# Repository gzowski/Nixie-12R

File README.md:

# Nixie-12R - Keyboard/GamePad

* Available to purchase from: https://www.etsy.com/uk/shop/PhoenixCustomBoards

* 11 key ortholinear keyboard
* 1 Rotary encoder in the top right
* OLED Display for displaying layer selected
* Pro Micro compatible
  
### [Info](#Info) || [Parts](#Parts) || [Assembly Guide](#Assembly-Guide)

## Info

* PCB Files within PCB folder, created with KiCad.
* VIA config export and via.json design files in VIA folder
* QMK firmware within QMK/QMK_Firmware/Keyboards/Nixie12r, can be pasted into a local copy of qmk repo and made.
* 3D printable case within Case folder

## Parts

| Part | Quantity     | Description                | 
| :-------- | :------- | :------------------------- |
| Diodes| 12  | Through-hole 1N4148 |
| Microcontroller | 1 | Pro-Micro compatible |
| MX Switches | 11 | Cherry MX compatible switches |
| EC11 | 1 | Rotary Encoder |
| MJTP1117 | 1 | Angled reset switch |
| Keycaps | 1 | 11x1u switches |
| OLED Display | 1 | 128x32 OLED (SSD1306) |

## Assembly Guide

* Insert all switches into the top plate and put to the side
* Diode installation: insert from top of the pcb so diodes are visible from the top
* Reset switch: insert switch on top and solder from underside, remove legs beforehand for clearance.
* Microcontroller needs to be positioned with the top facing the PCB, upsidedown (Test controller beforehand and flash firmware using QMK)
* Place OLED Display on top of PCB and solder from underside.
* Place the rotary encoder on the top side and solder all points ensuring it stays flush to the board.
* Press down the top plate with switches and stabalisers down on the middle plate ensuring that all the switches sit flush against the middle plate.
* Turn board over and proceed to solder switches to the board
* Connect USB to keyboard and check all keys are functional, this is assuming you've already flashed the firmware to the MCU.

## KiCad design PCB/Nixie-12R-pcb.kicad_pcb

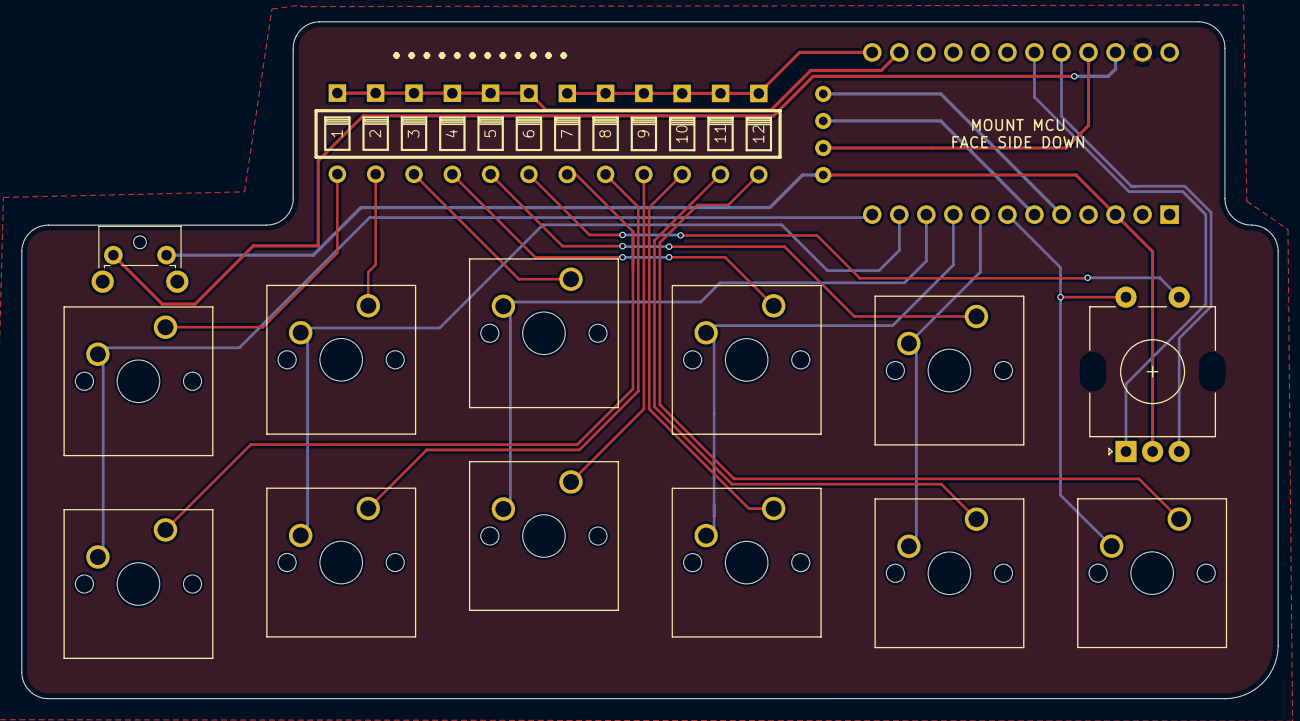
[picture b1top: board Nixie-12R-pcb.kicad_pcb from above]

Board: 2 copper layers, 118.1 x 63.6 mm, 27 parts (1 on the bottom side), 27 nets.

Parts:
1, 2: Diode
3, 4, 5, 6, 7, 8, 9, 10, 11, 12: VAL**; Diode
K1, K2, K3, K4, K5, K7, K8, K9, K10, K11, K12: Blank; SW_Cherry_MX_2.00u_PCB
K6-Rotary: RotaryEncoder_EC11
OLED1: OLED; OLED_v2.1
RST: SW_PUSH; SW_Tactile_SPST_Angled_MJTP1117
U1: ProMicro; ArduinoProMicro

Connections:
/Col_0: K1.2, K7.2, U1.12
/Col_1: K2.2, K8.2, U1.11
/Col_2: K3.2, K9.2, U1.10
/Col_3: K4.2, K10.2, U1.9
/Col_4: K5.2, K11.2, U1.8
/Col_5: K12.2, U1.7
/Row_0: 1.2, 2.2, 3.2, 4.2, 5.2, 6.2, U1.14
/Row_1: 7.2, 8.2, 9.2, 10.2, 11.2, 12.2, U1.13
GND2: K6-Rotary.C, OLED1.4, U1.3
unnamed: 1.1, K1.1
unnamed: 2.1, K2.1
unnamed: 3.1, K3.1
unnamed: 4.1, K4.1
unnamed: 5.1, K5.1
unnamed: 6.1, K6-Rotary.S1
unnamed: 7.1, K7.1
unnamed: 8.1, K8.1
unnamed: 9.1, K9.1
unnamed: 10.1, K10.1
unnamed: 11.1, K11.1
unnamed: 12.1, K12.1
ROTDEC: K6-Rotary.A, U1.19
ROTINC: K6-Rotary.B, U1.20
RST: RST.1, U1.22
SDA: OLED1.1, U1.5
SDL: OLED1.2, U1.6
VCC: OLED1.3, U1.21

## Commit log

2023-11-14 Tue Nov 14 11:46:46 AM GMT 2023
2023-11-14 Tue Nov 14 11:47:45 AM GMT 2023
2023-11-25 Sat Nov 25 11:00:44 PM GMT 2023
2023-11-25 Sat Nov 25 11:06:48 PM GMT 2023
2023-11-25 Sat Nov 25 11:07:54 PM GMT 2023
2023-11-25 Sat Nov 25 11:09:03 PM GMT 2023
2023-11-25 Sat Nov 25 11:10:11 PM GMT 2023
2023-11-25 Sat Nov 25 11:22:53 PM GMT 2023
